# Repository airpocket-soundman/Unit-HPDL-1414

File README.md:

# Unit-HPDL-1414
HPDL-1414をM5StackのUnitにする

# BOM
M5Stamp S3
HPDL-1414

# PIN接続

|No|HPDL1414|StampS3|GROVE|
|-|-|-|-|
|1|D6 DATA INPUT|G46|
|2|D5 DATA INPUT|G43|
|3|WR WRITE(1)|G42|
|3|WR WRITE(2)|G44|
|4|A1 DIGIT SELECT|G41|
|5|A0 DIGIT SELECT|G40|
|6|VDD||
|7|GND||
|8|D0 DATA INPUT|G1|
|9|D1 DATA INPUT|G3|
|10|D2 DATA INPUT|G5|
|11|D3 DATA INPUT|G7|
|12|D4 DATA INPUT|G9|
|13|SDA|G13|
|14|SDC|G14|

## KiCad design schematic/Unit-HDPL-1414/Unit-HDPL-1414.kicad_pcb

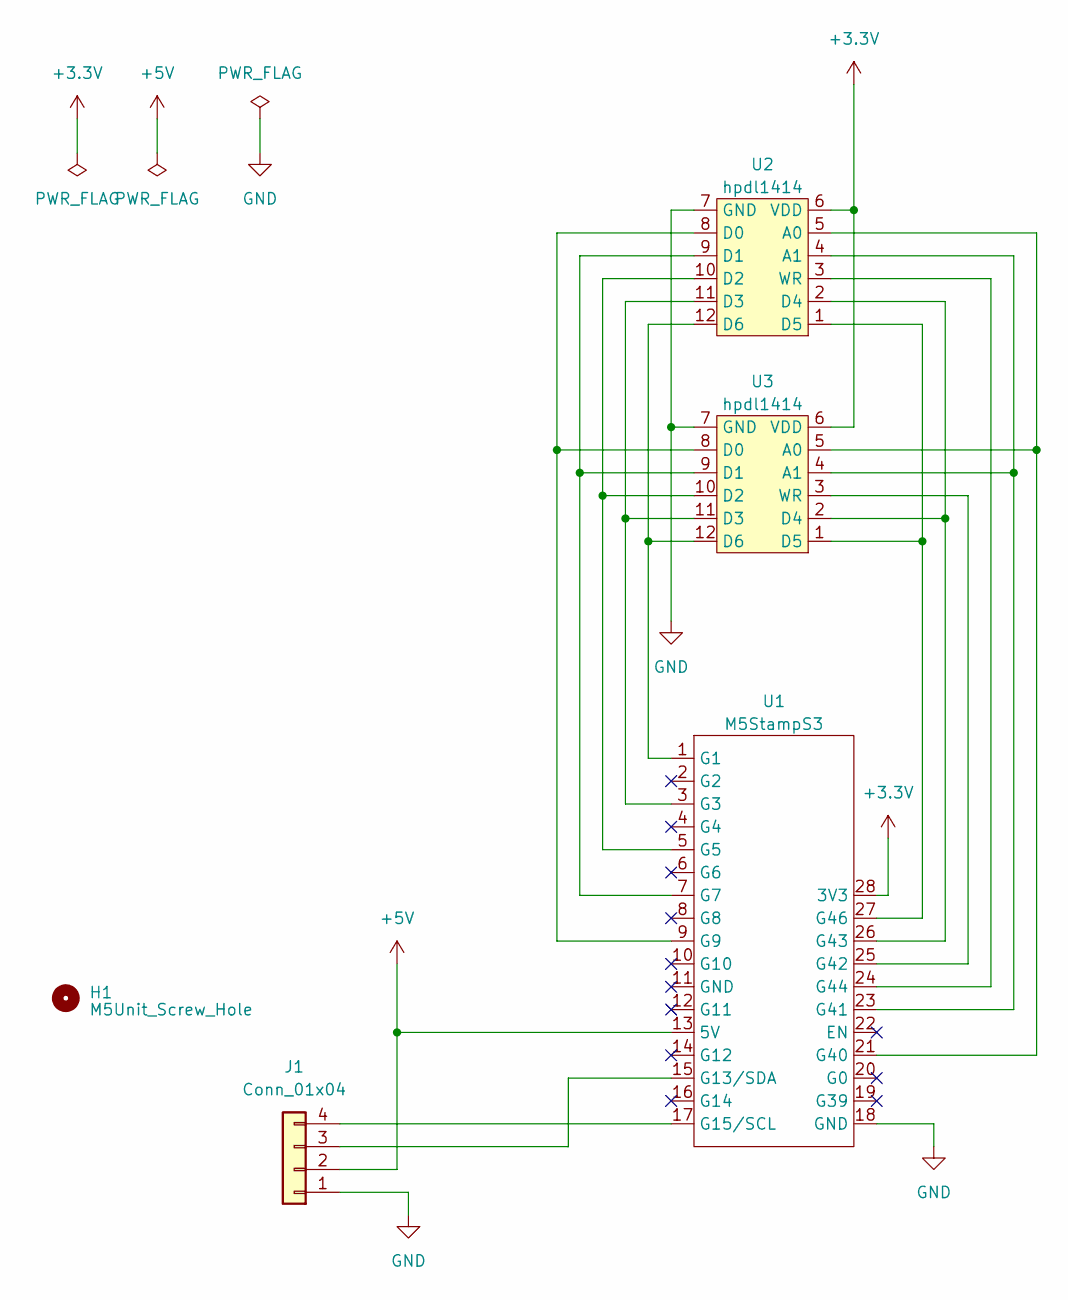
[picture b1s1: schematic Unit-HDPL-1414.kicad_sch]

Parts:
H1: M5Unit_Screw_Hole; unit_mounting_hole
J1: Conn_01x04; HY2.0-4P
U1: M5StampS3
U2, U3: hpdl1414; HPDL-1414

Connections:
+3.3V: U1.28 (3V3), U2.6 (VDD), U3.6 (VDD)
+5V: J1.2, U1.13 (5V)
GND: J1.1, U1.18 (GND), U2.7 (GND), U3.7 (GND)
unnamed: J1.3, U1.15 (G13/SDA)
unnamed: J1.4, U1.17 (G15/SCL)
unnamed: U1.1 (G1), U2.12 (D6), U3.12 (D6)
unnamed: U1.3 (G3), U2.11 (D3), U3.11 (D3)
unnamed: U1.5 (G5), U2.10 (D2), U3.10 (D2)
unnamed: U1.7 (G7), U2.9 (D1), U3.9 (D1)
unnamed: U1.9 (G9), U2.8 (D0), U3.8 (D0)
unnamed: U1.21 (G40), U2.5 (A0), U3.5 (A0)
unnamed: U1.23 (G41), U2.4 (A1), U3.4 (A1)
unnamed: U1.25 (G42), U3.3 (WR)
unnamed: U1.26 (G43), U2.2 (D4), U3.2 (D4)
unnamed: U1.24 (G44), U2.3 (WR)
unnamed: U1.27 (G46), U2.1 (D5), U3.1 (D5)

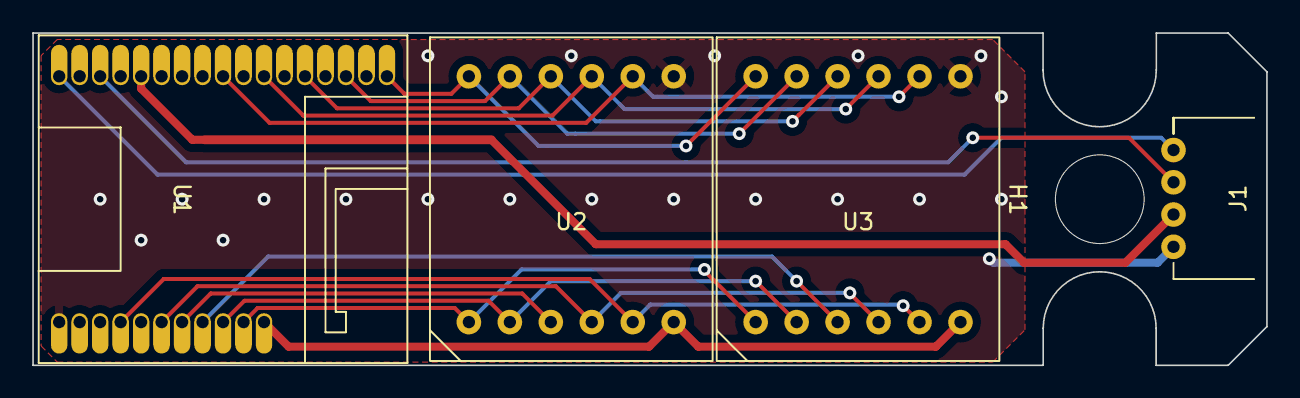
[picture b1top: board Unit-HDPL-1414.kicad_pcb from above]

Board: 2 copper layers, 76.5 x 20.6 mm, 5 parts (0 on the bottom side), 16 nets.

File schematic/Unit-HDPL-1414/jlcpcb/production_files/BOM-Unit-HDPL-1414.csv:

Comment,Designator,Footprint,LCSC
H1,M5Unit_Screw_Hole,unit_mounting_hole,,,0,0
J1,Conn_01x04,HY2.0-4P,,,0,0
U1,M5StampS3,M5StampS3,,,0,0
U2,hpdl1414,HPDL-1414,,,0,0
U3,hpdl1414,HPDL-1414,,,0,0

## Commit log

2024-06-18 schematic作成中
2024-06-25 schematic src
2024-06-26 slave master コード作成中
2024-06-27 mastaer_slave_uiflowblock
2024-06-28 基板ピン配置ミス修正
2024-07-18 回路図修正
2024-07-18 コード見直し等
2024-07-18 test
2024-07-19 カスタムブロック修正
